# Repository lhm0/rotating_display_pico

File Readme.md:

# Rotating Display Pico

## Abstract: 
The Rotating Display Pico is a compact disc-sized device that rotates quietly using a CD motor. It features 56 white LEDs which are controlled by a raspberry pi pico. The device can display animated images as well as time and weather data sourced from the internet. It is wirelessly powered and controlled via a user-friendly web interface. The device uses off-the-shelf components and is easy to assemble in a DIY electronics project.

<p align="center"> 

</p> 

## 1. Description of the device

The Rotating Display pico device comprises two primary units: a power supply unit and a display board (**figure 1**). Both are circular in design, with a diameter of 120mm, similar to the dimensions of a standard Compact Disk. The display board is rotated by a CD motor. Energy is wirelessly transmitted from the power supply unit to the display board, eliminating the need for wired connections.

**Figure 1:  Rotating Display pico assembly.** The lower PCB is the power supply with wireless power transmission, the upper PCB is the display board.

The display board is equipped with a row containing 56 white LEDs. The LED operations are controlled by a Raspberry Pi Pico W, which at the same time generates the display content, maintains a Wi-Fi connection to the internet, and provides a web user interface. Images (including animated images) can be stored on and loaded from a micro SMD card. 

This internet connection allows the device to retrieve the time from a time server, ensuring time accuracy. It also allows for the acquisition of weather data. Device operation is managed through a web interface (**figure 2**), accessible from any web browser. The interface allows users to manage login credentials, upload image files to the display, and control image and configuration files through a file manager.

**Figure 2:** The **web user interface** allows for operating mode selection and device configuration.

## 2. Operating modes

When switched on, the device tries to connect to a known wifi. If no valid wifi credentials are found, the unit will be configured as wifi access point. In this mode, a computer or mobile device can be connected, directly (SSID: RD56m, no password). 

Once the wifi connection has been established, the unit will display its IP address on the  home page of the device (**figure 3**). Enter this address in your web browser. This will load the web user interface and will allow you to configure your local wifi.

**Figure 3: home page.**

There are several operating modes that display time and weather information (**figure 4**). The logo clock mode integrates a customizable image into the clock face. The image can be easily uploaded from the user interface. The same is true for the analog clock, which uses a customizable clock face in the background.

**Figure 4: operating modes.** Modes can be selected and configured through the web interface.

## 3. Mechanical design

The device consists of two assemblies: power supply and display. The power supply board is also the base plate, which can either be placed on a flat surface or hung on a wall. A standard CD motor is attached to this board so that the CD tray above the power supply board can accommodate the display assembly. The display board is fixed with two M2 x 6 mm screws. Furthermore, the base plate carries a potentiometer to control the motor speed as well as an on/off switch for the motor.

**Figure 5: Power Supply Board** with CD motor (middle), 12 V power jack (lower side), and speed potentiometer

An important requirement for the display board is that the center of mass of the unit is exactly in the middle, on the axis of rotation of the motor. This is the only way to ensure smooth and vibration-free running of the display. To achieve this, the electronic components are arranged symmetrically to the vertical axis of symmetry (**figure 7**). This initially ensures that the center of gravity lies on this vertical axis. However, since the components cannot be distributed symmetrically to the horizontal axis of symmetry, the center of gravity must be shifted to the center along this axis using balancing weights. For this purpose, two M3x6mm screws with two nuts each are placed to the right and left of the micro SD card slot. The overall balancing result is very good, but can certainly be further optimized.

**Figure 6: Display Board.** Main components are the LED row, the Raspberry Pi Pico W microcontroller, and two driver chips for the LEDs. On the backside of the board the secondary coil of the wireless power supply is attached.

**Figure 7:** The components of the display board are arranged symmetrically to the vertical axis of symmetry. Balancing weights are used to shift the center of gravity to the middle of the disk.

The LED row consists of 56 discrete, rectangular LEDs. The components each have a width of 2.0 mm and can be lined up with little spacing. However, the row of LEDs is not arranged symmetrically to the center of the disk, but shifted by 0.5 mm. If the display panel is rotated by 180 degrees, this decentration causes the LEDs to be shifted by exactly 1 mm from the original grid (**figure 8**). This results in rotational interlacing: the radial resolution is increased from 2 to 1 mm. At the same time, the perceived frame rate also increases by a factor of 2..

**Figure 8:** The LED row is shifted radially by half a LED width. The two halfs of the row generate an interlacing effect, which doubles both the radial resolution and the image frame rate.

The LEDs must output the image information at exactly the right position with each rotation. For spatial alignment of the image, a trigger signal is generated at a defined position for each rotation, which triggers the sequential, clocked output of the pixels. The trigger signal must be spatially very stable, otherwise no smooth image can be generated. It turned out that a Hall sensor is best suited for this purpose. It is located on the left-hand side of the disk at the 10:30 clock position (see **figure 6**, left picture). The magnet is glued into a hole of the power supply PCB (see figure 5, left picture, 2 o'clock position).

## 4. Electronics architecture

The distribution of the electronic circuitry between the two assemblies is shown in **figure 9**. The power supply assembly contains a Royer converter for wireless power transfer to the display assembly and an adjustment of the motor speed. The 56 LEDs of the display assembly are arranged in a matrix and are multiplexed by the microcontroller. The displayed content is either loaded from the internet via Wifi (time, weather data) or generated from image data locally, which is stored on a micro SD card.

## 5. Power supply board

The core of the power supply is a Royer converter for wireless power transfer. An excellent article on the operation and design of the circuit can be found at [Mikrocontroller.net](https://www.mikrocontroller.net/articles/Royer_Converter) (German) and the circuit was taken from there. Two transistors are alternately switched (push pull operation) so that a current flows through one half of the coil at a time. The coil belongs to a resonant circuit with a resonant frequency of about 120 kHz. The control voltage for the transistors is obtained via a coupling coil (**figure 10**). The secondary coil is located below the display board (see **figure 6**, right).

The Royer circuit uses very few components. However, the coil is quite complex. It is a bifilar coil, where the two halves are interleaved. In addition, the coupling coil must be connected with the correct polarity, otherwise the two transistors will be destroyed. In the early stages of development, the coil was wound with copper wire. However, this solution was quite difficult to reproduce, so in the final design the coils (bifilar primary coil, coupling coil, secondary coil) were implemented as a printed circuit (see **figure 5**, left and **figure 6** right). The circuit was found to have surprisingly high and perfectly adequate transmission efficiency, although the quality factor of the printed coils is inevitably compromised. The Royer converter with the printed coil assembly is absolutely safe to rebuild. It is supplied with 12 V. 

**Figure 10: Royer converter**. Compare [Mikrocontroller.net](https://www.mikrocontroller.net/articles/Royer_Converter) for reference.

There is also a circuit for supplying the CD motor on the power supply board. By means of an adjustable voltage regulator, a variable voltage between 1.7V and 6.0V is generated. It can be adjusted via a potentiometer. The voltage range corresponds to the specified operating range of the CD motor. The supply of the motor can be interrupted with a switch, for example to allow programming of the microcontrollers.

## 6. Display Board
The 56 LEDs of the display are arranged in a matrix with 7 columns and 8 rows (**figure 11**). The microcontroller activates the columns successively and sets the rows for each columns as needed.

The columns are activated by connecting them to +5V by means of a p-channel MOSFET, each. The control of the MOSFETs needs 5V logic (+5V = off, 0V = on), while the Raspberry pi pico operates with 3.3V logic. Therefore, levels need to be shifted, which is done with the 74HCT138. The circuit is a 3 bit decoder. One of the 8 outputs can be selected by setting the 3 inputs accordingly. Only the selected output goes to "L", while all other outputs are "H". This ensures, that only one LED column can be selected at a time.

The 8 rows are activated by means of a Darlington transistor each. The transistors are arraged in an array (ULN2803). The resistors set the LED current to about 60 mA. This is well with the [specification of the LEDs](https://www.led1.de/shop/files/Datenblaetter/Rechteckig/WEHWW02-D1M.pdf).

**Figure 11: Schematic of the Display Board**

The timing of the display is critical in order to generate stable largely flicker free grey level images. **Figure 12** shows the timing sequence. The display rotates with a frequency of up to 10 Hz. The Hall sensor generates a reference signal once it is within reach of the static magnet. Within the 100 ms per revolution, 240 lines with 56 pixels each are successively displayed. Each line will be displayed for 100ms/240 = 420µs. In order to generate grey levels, each pixel is split into 8 "sub pixels". If all of the subpixels are "on", the intensity of the pixel will be maximal, if 4 subpixels are "on" and 4 subpixels are "off", intensity of the pixel will be medium, and if all subpixels are "off", intensity will be zero. The time per subpixel is 420µs/8 = 52µs. Within this time, the multiplexing of the LEDs has to happen. Each column of the matrix will be displayed for 52µs/7 = 7.5µs. 

**Figure 12: Timing of the LED control.** Within the time per revolution of 100ms, 240 lines with 8 grey levels are displayed. 

The high speed of the multiplexing has quite some implications. The electronics and its setup needs to allow for very short and steep 60 mA current pulses. In order to manage electromagnetic interference, a 4 layer board has been used. The two inner layers are grounding planes, all vias have a grounding "companion", in order to ensure [proper current return paths](https://www.youtube.com/live/ySuUZEjARPY?si=sn-svxhxvuI3ehGK). Furthermore, the microcontroller needs to control the output lines in a strict and very fast time regime.

Fortunately, the RP2040 microcontroller has a powerful unit for controlling the input and outputs (PIO = programmable IO) (**figure 13**). This unit is used to manage the multiplexing and decouple its timing from the processor and its interrupts as much as possible. The solution ensures not only the necessary very high speed for the multiplexing, but also generates a stable time regime.

**Figure 13: RP2040 programmable IO (PIO).** The unit allows for fast multiplexing of the LEDs. 

The full circuit diagram of the display board is shown in **figure 14**. All details can be obtained from the [GitHub repository](https://github.com/lhm0/rotating_display_pico/tree/master).

**Figure 14: Circuit diagram of the display board**

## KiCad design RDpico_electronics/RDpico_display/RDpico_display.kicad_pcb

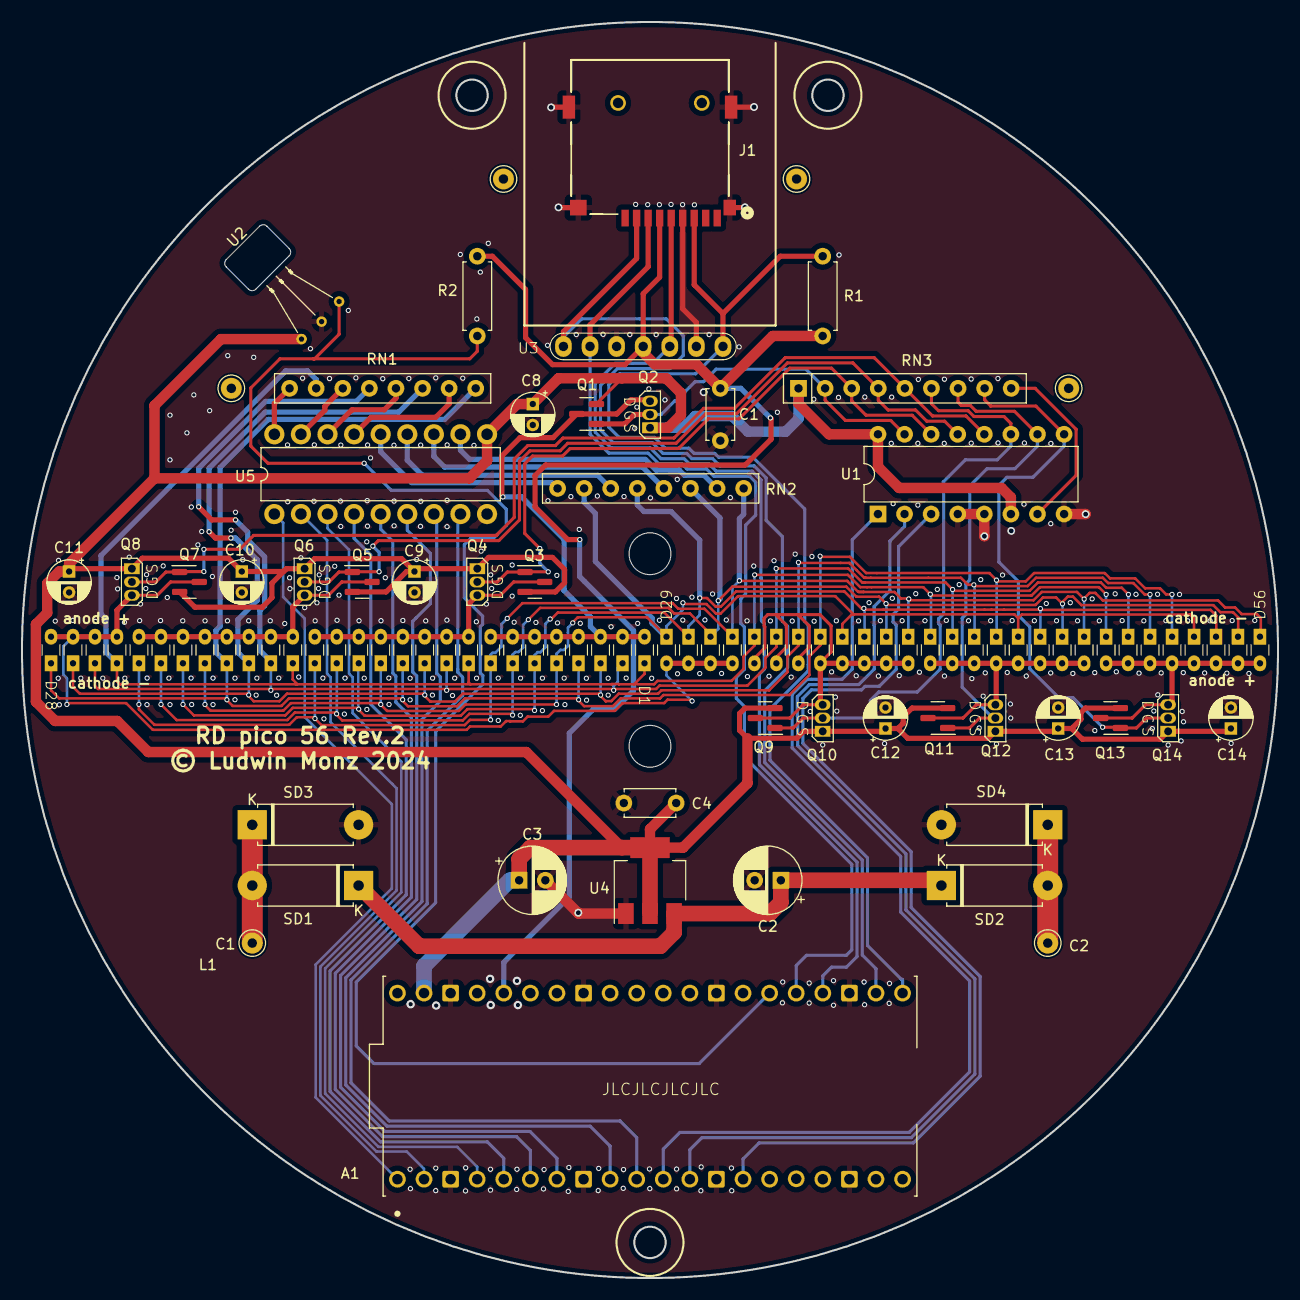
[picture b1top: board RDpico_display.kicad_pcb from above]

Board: 4 copper layers, 120.0 x 120.0 mm, 98 parts (0 on the bottom side), 53 nets.

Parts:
A1: SC0918; MODULE_SC0918
C1, C4: 100nF; C_Disc_D4.7mm_W2.5mm_P5.00mm
C2: 220µF; CP_Radial_D6.3mm_P2.50mm
C3: 100µF; CP_Radial_D6.3mm_P2.50mm
C8, C9, C10, C11, C12, C13, C14: 10µ; CP_Radial_D4.0mm_P2.00mm
D1, D2, D3, D4, D5, D6, D7, D8, D9, D10, D11, D12, D13, D14, D15, D16, D17, D18, D19, D20, D21, D22, D23, D24, D25, D26, D27, D28, D29, D30, D31, D32, D33, D34, D35, D36, D37, D38, D39, D40, D41, D42, D43, D44, D45, D46, D47, D48, D49, D50, D51, D52, D53, D54, D55, D56: LED; LED_rect_2x3
J1: Micro_SD_Card; microSD_SMD
L1: Coil; coil_large
Q1, Q3, Q5, Q7, Q9, Q11, Q13: IRLML6401; SOT-23
Q2, Q4, Q6, Q8, Q10, Q12, Q14: BS250; BS250P
R1: 10k; R_Axial_DIN0207_L6.3mm_D2.5mm_P7.62mm_Horizontal
R2: 2.2k; R_Axial_DIN0207_L6.3mm_D2.5mm_P7.62mm_Horizontal
RN1, RN2: 47; RN4
RN3: 47k; R_Array_SIP9
SD1, SD2, SD3, SD4: 1N5818; D_5W_P10.16mm_Horizontal
U1: 74HCT138; DIP-16_W7.62mm
U2: A3144; A3144_front
U3: 7pin
U4: LM1117-5.0; SOT-223-3_TabPin2
U5: ULN2803A

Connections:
+3.3V: A1.36 (3V3_OUT), C1.1, J1.4 (VDD), R1.1, R2.2, U3.4 (VCC)
+5V: A1.39 (VSYS), C3.1, C4.2, C8.1, C9.1, C10.1, C11.1, C12.1, C13.1, C14.1, Q1.2 (S), Q2.3 (S), Q3.2 (S), Q4.3 (S), Q5.2 (S), Q6.3 (S), Q7.2 (S), Q8.3 (S), Q9.2 (S), Q10.3 (S), Q11.2 (S), Q12.3 (S), Q13.2 (S), Q14.3 (S), RN3.1 (common), U1.6 (E2), U1.16 (VCC), U2.1 (Vcc), U4.2 (VO), U5.10 (COM)
GND: A1.3 (GND), A1.8 (GND), A1.13 (GND), A1.18 (GND), A1.23 (GND), A1.28 (GND), A1.33 (AGND), A1.38 (GND), C1.2, C2.2, C3.2, C4.1, C8.2, C9.2, C10.2, C11.2, C12.2, C13.2, C14.2, J1.6 (VSS), J1.10 (S), J1.11 (S), J1.12 (S), J1.13 (S), SD3.2 (A), SD4.2 (A), U1.4 (~E0), U1.5 (~E1), U1.8 (GND), U2.2 (Ground), U3.2 (GND), U3.5 (GND), U4.1 (GND), U5.9 (GND)
LED_c0: D1.1 (K), D9.1 (K), D17.1 (K), D25.1 (K), D33.1 (K), D41.1 (K), D49.1 (K), RN1.2
LED_c1: D2.1 (K), D10.1 (K), D18.1 (K), D26.1 (K), D34.1 (K), D42.1 (K), D50.1 (K), RN1.4
LED_c2: D3.1 (K), D11.1 (K), D19.1 (K), D27.1 (K), D35.1 (K), D43.1 (K), D51.1 (K), RN1.6
LED_c3: D4.1 (K), D12.1 (K), D20.1 (K), D28.1 (K), D36.1 (K), D44.1 (K), D52.1 (K), RN1.8
LED_c4: D5.1 (K), D13.1 (K), D21.1 (K), D29.1 (K), D37.1 (K), D45.1 (K), D53.1 (K), RN2.2
LED_c5: D6.1 (K), D14.1 (K), D22.1 (K), D30.1 (K), D38.1 (K), D46.1 (K), D54.1 (K), RN2.4
LED_c6: D7.1 (K), D15.1 (K), D23.1 (K), D31.1 (K), D39.1 (K), D47.1 (K), D55.1 (K), RN2.6
LED_c7: D8.1 (K), D16.1 (K), D24.1 (K), D32.1 (K), D40.1 (K), D48.1 (K), D56.1 (K), RN2.8
LED_r0: Q1.1 (G), Q2.2 (G), RN3.2 (R1), U1.15 (~Y0)
LED_r1: Q3.1 (G), Q4.2 (G), RN3.3 (R2), U1.14 (~Y1)
LED_r2: Q5.1 (G), Q6.2 (G), RN3.4 (R3), U1.13 (~Y2)
LED_r3: Q7.1 (G), Q8.2 (G), RN3.5 (R4), U1.12 (~Y3)
LED_r4: Q9.1 (G), Q10.2 (G), RN3.6 (R5), U1.11 (~Y4)
LED_r5: Q11.1 (G), Q12.2 (G), RN3.7 (R6), U1.10 (~Y5)
LED_r6: Q13.1 (G), Q14.2 (G), RN3.8 (R7), U1.9 (~Y6)
LED_r7: RN3.9 (R8), U1.7 (~Y7)
unnamed: A1.1 (GP0), U5.1 (I1)
unnamed: A1.2 (GP1), U5.2 (I2)
unnamed: A1.4 (GP2), U5.3 (I3)
unnamed: A1.5 (GP3), U5.4 (I4)
unnamed: A1.6 (GP4), U5.5 (I5)
unnamed: A1.7 (GP5), U5.6 (I6)
unnamed: A1.9 (GP6), U5.7 (I7)
unnamed: A1.10 (GP7), U5.8 (I8)
unnamed: A1.11 (GP8), U1.1 (A0)
unnamed: A1.12 (GP9), U1.2 (A1)
unnamed: A1.14 (GP10), U1.3 (A2)
unnamed: A1.26 (GP20), R2.1, U2.3 (Output)
unnamed: D1.2 (A), D2.2 (A), D3.2 (A), D4.2 (A), D5.2 (A), D6.2 (A), D7.2 (A), D8.2 (A), Q1.3 (D), Q2.1 (D)
unnamed: D9.2 (A), D10.2 (A), D11.2 (A), D12.2 (A), D13.2 (A), D14.2 (A), D15.2 (A), D16.2 (A), Q3.3 (D), Q4.1 (D)
unnamed: D17.2 (A), D18.2 (A), D19.2 (A), D20.2 (A), D21.2 (A), D22.2 (A), D23.2 (A), D24.2 (A), Q5.3 (D), Q6.1 (D)
unnamed: D25.2 (A), D26.2 (A), D27.2 (A), D28.2 (A), D29.2 (A), D30.2 (A), D31.2 (A), D32.2 (A), Q7.3 (D), Q8.1 (D)
unnamed: D33.2 (A), D34.2 (A), D35.2 (A), D36.2 (A), D37.2 (A), D38.2 (A), D39.2 (A), D40.2 (A), Q9.3 (D), Q10.1 (D)
unnamed: D41.2 (A), D42.2 (A), D43.2 (A), D44.2 (A), D45.2 (A), D46.2 (A), D47.2 (A), D48.2 (A), Q11.3 (D), Q12.1 (D)
unnamed: D49.2 (A), D50.2 (A), D51.2 (A), D52.2 (A), D53.2 (A), D54.2 (A), D55.2 (A), D56.2 (A), Q13.3 (D), Q14.1 (D)
unnamed: L1.1, SD1.2 (A), SD3.1 (K)
unnamed: C2.1, SD1.1 (K), SD2.1 (K), U4.3 (VI)
unnamed: L1.2, SD2.2 (A), SD4.1 (K)
unnamed: RN1.1, U5.18 (O1)
unnamed: RN1.3, U5.17 (O2)
unnamed: RN1.5, U5.16 (O3)
unnamed: RN1.7, U5.15 (O4)
unnamed: RN2.1, U5.14 (O5)
unnamed: RN2.3, U5.13 (O6)
unnamed: RN2.5, U5.12 (O7)
unnamed: RN2.7, U5.11 (O8)
SD_CS: A1.22 (GP17), J1.2 (DAT3/CD), U3.7 (CS)
SD_MISO: A1.21 (GP16), J1.7 (DAT0), R1.2, U3.1 (MISO)
SD_MOSI: A1.25 (GP19), J1.3 (CMD), U3.6 (MOSI)
SD_SCK: A1.24 (GP18), J1.5 (CLK), U3.3 (SCK)

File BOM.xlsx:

BOM Rotating Display Pico
# | Reference | Qty | Description | source
1 | A1 | 1 | Raspberry Pi Pico W | https://www.raspberrypi.com/products/raspberry-pi-pico/
2 | C1, C4 | 2 | 100nF, | https://www.digikey.com/short/2bw9dzmp
3 | C2 | 1 | 220µF | https://www.digikey.com/short/hrdj5tbz
4 | C3 | 1 | 100µF | https://www.digikey.com/short/mfjrnd3m
5 | C8, C9, C10, C11, C12, C13, C14 | 7 | 10µ | https://www.digikey.com/short/zchpnfr9
6 | D1, D2, D3, D4, D5, D6, D7, D8, D9, D10, D11, D12, D13, D14, D15, D16, D17, D18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 | 56 | LED | https://www.led1.de/shop/standard-leds/led-rechteckig-ultrah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
7 | J1 | 1 | Micro_SD_Card Slot | https://www.digikey.com/short/5tpr3ntn
9 | Q1, Q3, Q5, Q7, Q9, Q11, Q13 | 7 | IRLML6401 | https://www.digikey.com/short/mmb8j7pn
10 | Q2, Q4, Q6, Q8, Q10, Q12, Q14 | 7 | BS250 | https://www.digikey.com/short/m88p5n9d
11 | R1 | 1 | 10k | generic
12 | R2 | 1 | 2.2k | generic
13 | RN1, RN2 | 2 | 47 | https://www.digikey.com/short/ddr9td25
14 | RN3 | 1 | 47k | https://www.digikey.com/short/2vwz5frm
15 | SD1, SD2, SD3, SD4 | 4 | 1N5818 | generic
16 | U1 | 1 | 74HCT138 | https://www.digikey.com/short/bbtft5nn
17 | U2 | 1 | A3144 | Amazon
19 | U4 | 1 | LM1117-5.0 | https://www.digikey.com/short/zrwjc997
20 | U5 | 1 | ULN2803A | https://www.digikey.com/short/pjrb5nj3
 | PCB |  | 4 layer PCB | various sources, for example JLCPCB.com

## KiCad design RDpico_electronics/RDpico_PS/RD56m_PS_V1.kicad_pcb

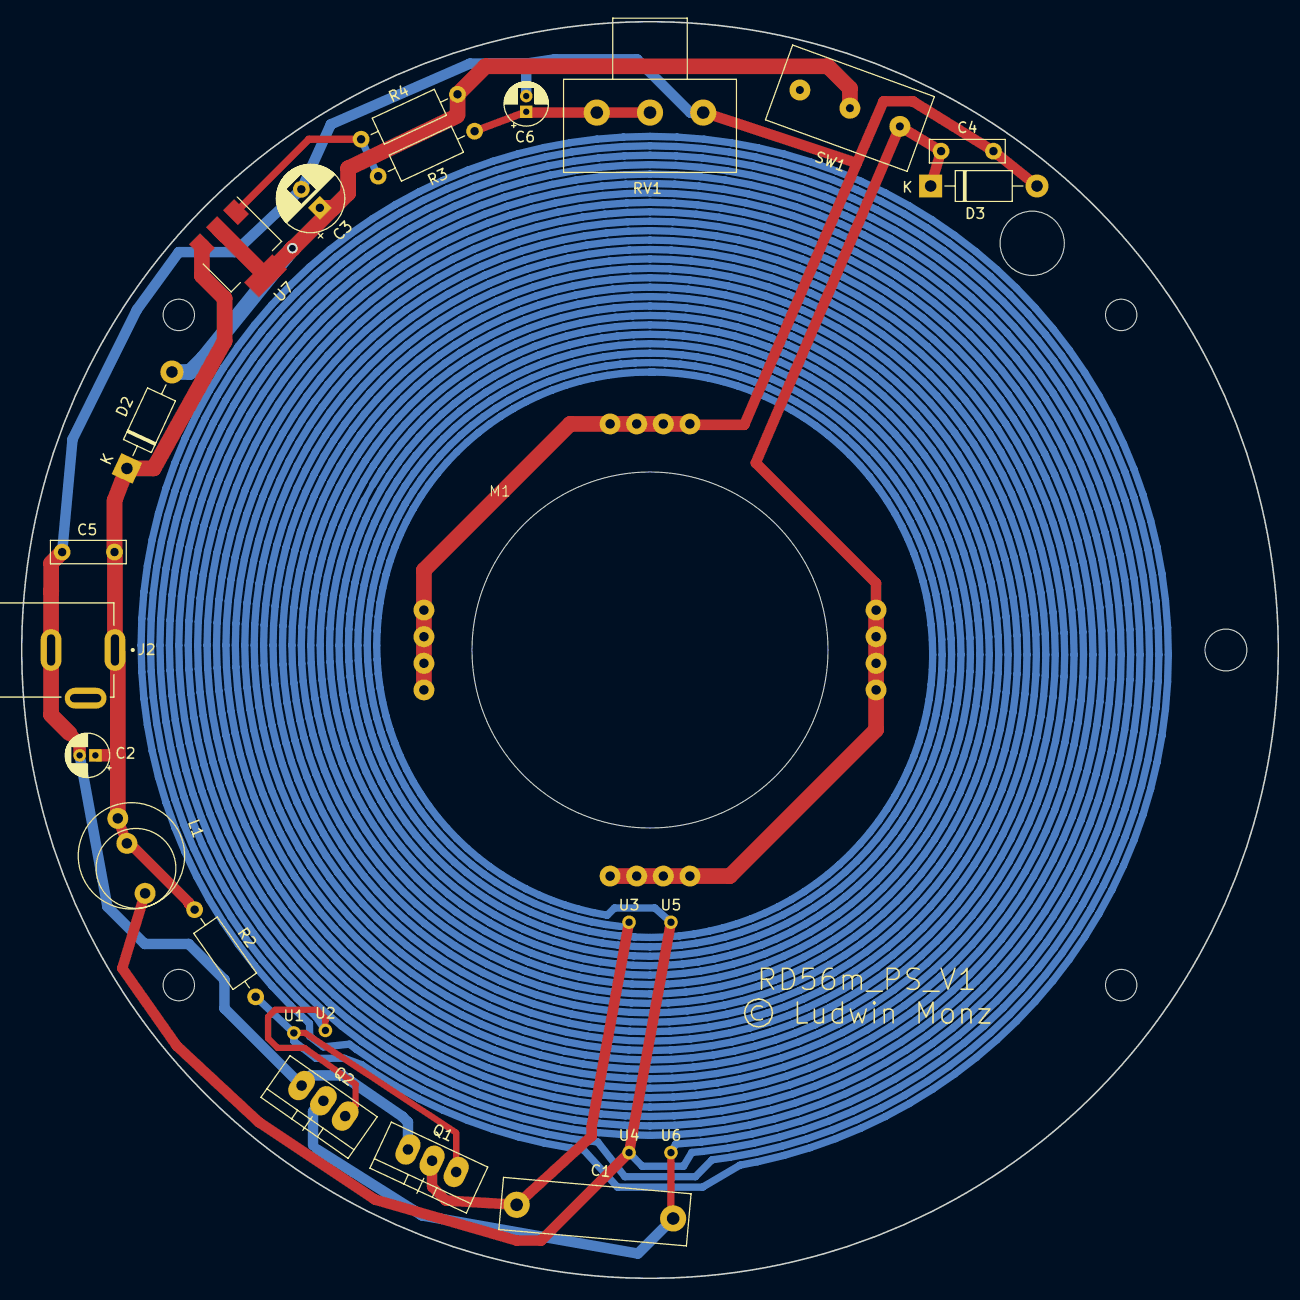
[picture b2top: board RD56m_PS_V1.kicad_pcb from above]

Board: 2 copper layers, 120.0 x 120.0 mm, 25 parts (0 on the bottom side), 8 nets.

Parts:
C1: 33nF; MKP10_630V
C2: 10µ, 50V; CP_Radial_D4.0mm_P1.50mm
C3: 100µ; CP_Radial_D6.3mm_P2.50mm
C4, C5: 100nF; C_Rect_L7.0mm_W2.0mm_P5.00mm
C6: 10µ; CP_Radial_D4.0mm_P1.50mm
D2, D3: 1N4001; D_DO-41_SOD81_P10.16mm_Horizontal
J2: Barrel_Jack_Switch_Pin3Ring; GRAVITECH_CON-SOCJ-2155
L1: 330µH; L_vertical12
M1: Motor_DC; motor_tray
Q1, Q2: NPN; TO220_vertikal
R2: 2k2; R_Axial_DIN0207_L6.3mm_D2.5mm_P10.16mm_Horizontal
R3: 120; R_Axial_DIN0207_L6.3mm_D2.5mm_P10.16mm_Horizontal
R4: 47; R_Axial_DIN0207_L6.3mm_D2.5mm_P10.16mm_Horizontal
RV1: 470; Poti_10mm
SW1: SW_DPDT_x2; Switch1
U1, U2, U3, U4, U5, U6: Pin-Connector; Pin_2mm
U7: AP1117-ADJ; SOT-223-3_TabPin2

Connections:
+12V: C2.1, C5.1, D2.1 (K), J2.1, L1.1, L1.3, R2.2, U7.3 (VI)
GND: C2.2, C3.2, C4.2, C5.2, C6.2, D3.2 (A), J2.3, M1.2 (-), Q1.3 (E), Q2.3 (E), RV1.1
unnamed: C6.1, R4.2, RV1.2, RV1.3
unnamed: C3.1, D2.2 (A), R3.1, SW1.2 (B), U7.2 (VO)
unnamed: C4.1, D3.1 (K), M1.1 (+), SW1.3 (C)
unnamed: Q1.1 (B), Q2.1 (B), R2.1, U1.1 (Pin1), U2.1 (Pin1)
unnamed: C1.1, C1.2, L1.2, Q1.2 (C), Q2.2 (C), U3.1 (Pin1), U4.1 (Pin1), U5.1 (Pin1), U6.1 (Pin1)
unnamed: R3.2, R4.1, U7.1 (ADJ)

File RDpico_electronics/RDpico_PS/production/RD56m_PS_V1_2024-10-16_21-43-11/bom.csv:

Designator,Footprint,Quantity,Value,LCSC Part #
C1,MKP10_630V,1,33nF,
C2,CP_Radial_D4.0mm_P1.50mm,1,"10µ, 50V",C13585
C3,CP_Radial_D6.3mm_P2.50mm,1,100µ,
"C4, C5",C_Rect_L7.0mm_W2.0mm_P5.00mm,2,100nF,
C6,CP_Radial_D4.0mm_P1.50mm,1,10µ,
"D2, D3",D_DO-41_SOD81_P10.16mm_Horizontal,2,1N4001,
J2,GRAVITECH_CON-SOCJ-2155,1,Barrel_Jack_Switch_Pin3Ring,
L1,L_vertical12,1,330µH,
M1,motor_tray,1,Motor_DC,
"Q1, Q2",TO220_vertikal,2,NPN,
R2,R_Axial_DIN0207_L6.3mm_D2.5mm_P10.16mm_Horizontal,1,2k2,
R3,R_Axial_DIN0207_L6.3mm_D2.5mm_P10.16mm_Horizontal,1,120,
R4,R_Axial_DIN0207_L6.3mm_D2.5mm_P10.16mm_Horizontal,1,47,
RV1,Poti_10mm,1,470,
SW1,Switch1,1,SW_DPDT_x2,
"U1, U2, U3, U4, U5, U6",Pin_2mm,6,Pin-Connector,
U7,SOT-223-3_TabPin2,1,AP1117-ADJ,

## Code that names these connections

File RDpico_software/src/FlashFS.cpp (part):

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#include <SD.h>
#include <SPI.h>

#define PIN_SD_MOSI       19
#define PIN_SD_MISO       16
#define PIN_SD_SCK        18
#define PIN_SD_SS         17

// Constructor
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
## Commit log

2024-10-27 added images
2024-10-27 more images
2024-10-27 some more photos
2024-10-27 first paragraph of readme.md
2024-10-28 BOM added
2024-10-28 BOM completed
2024-10-28 correct POSIX for daylight saving time in Germany
2024-10-29 firmware.uf2 moved to root
2024-12-12 update production files

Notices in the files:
RDpico_software/src/FlashFS.cpp:
© Ludwin Monz
License: Creative Commons Attribution - Non-Commercial - Share Alike (CC BY-NC-SA)
RDpico_electronics/RDpico_display/RDpico_display.kicad_pcb:
© Ludwin Monz 2024
